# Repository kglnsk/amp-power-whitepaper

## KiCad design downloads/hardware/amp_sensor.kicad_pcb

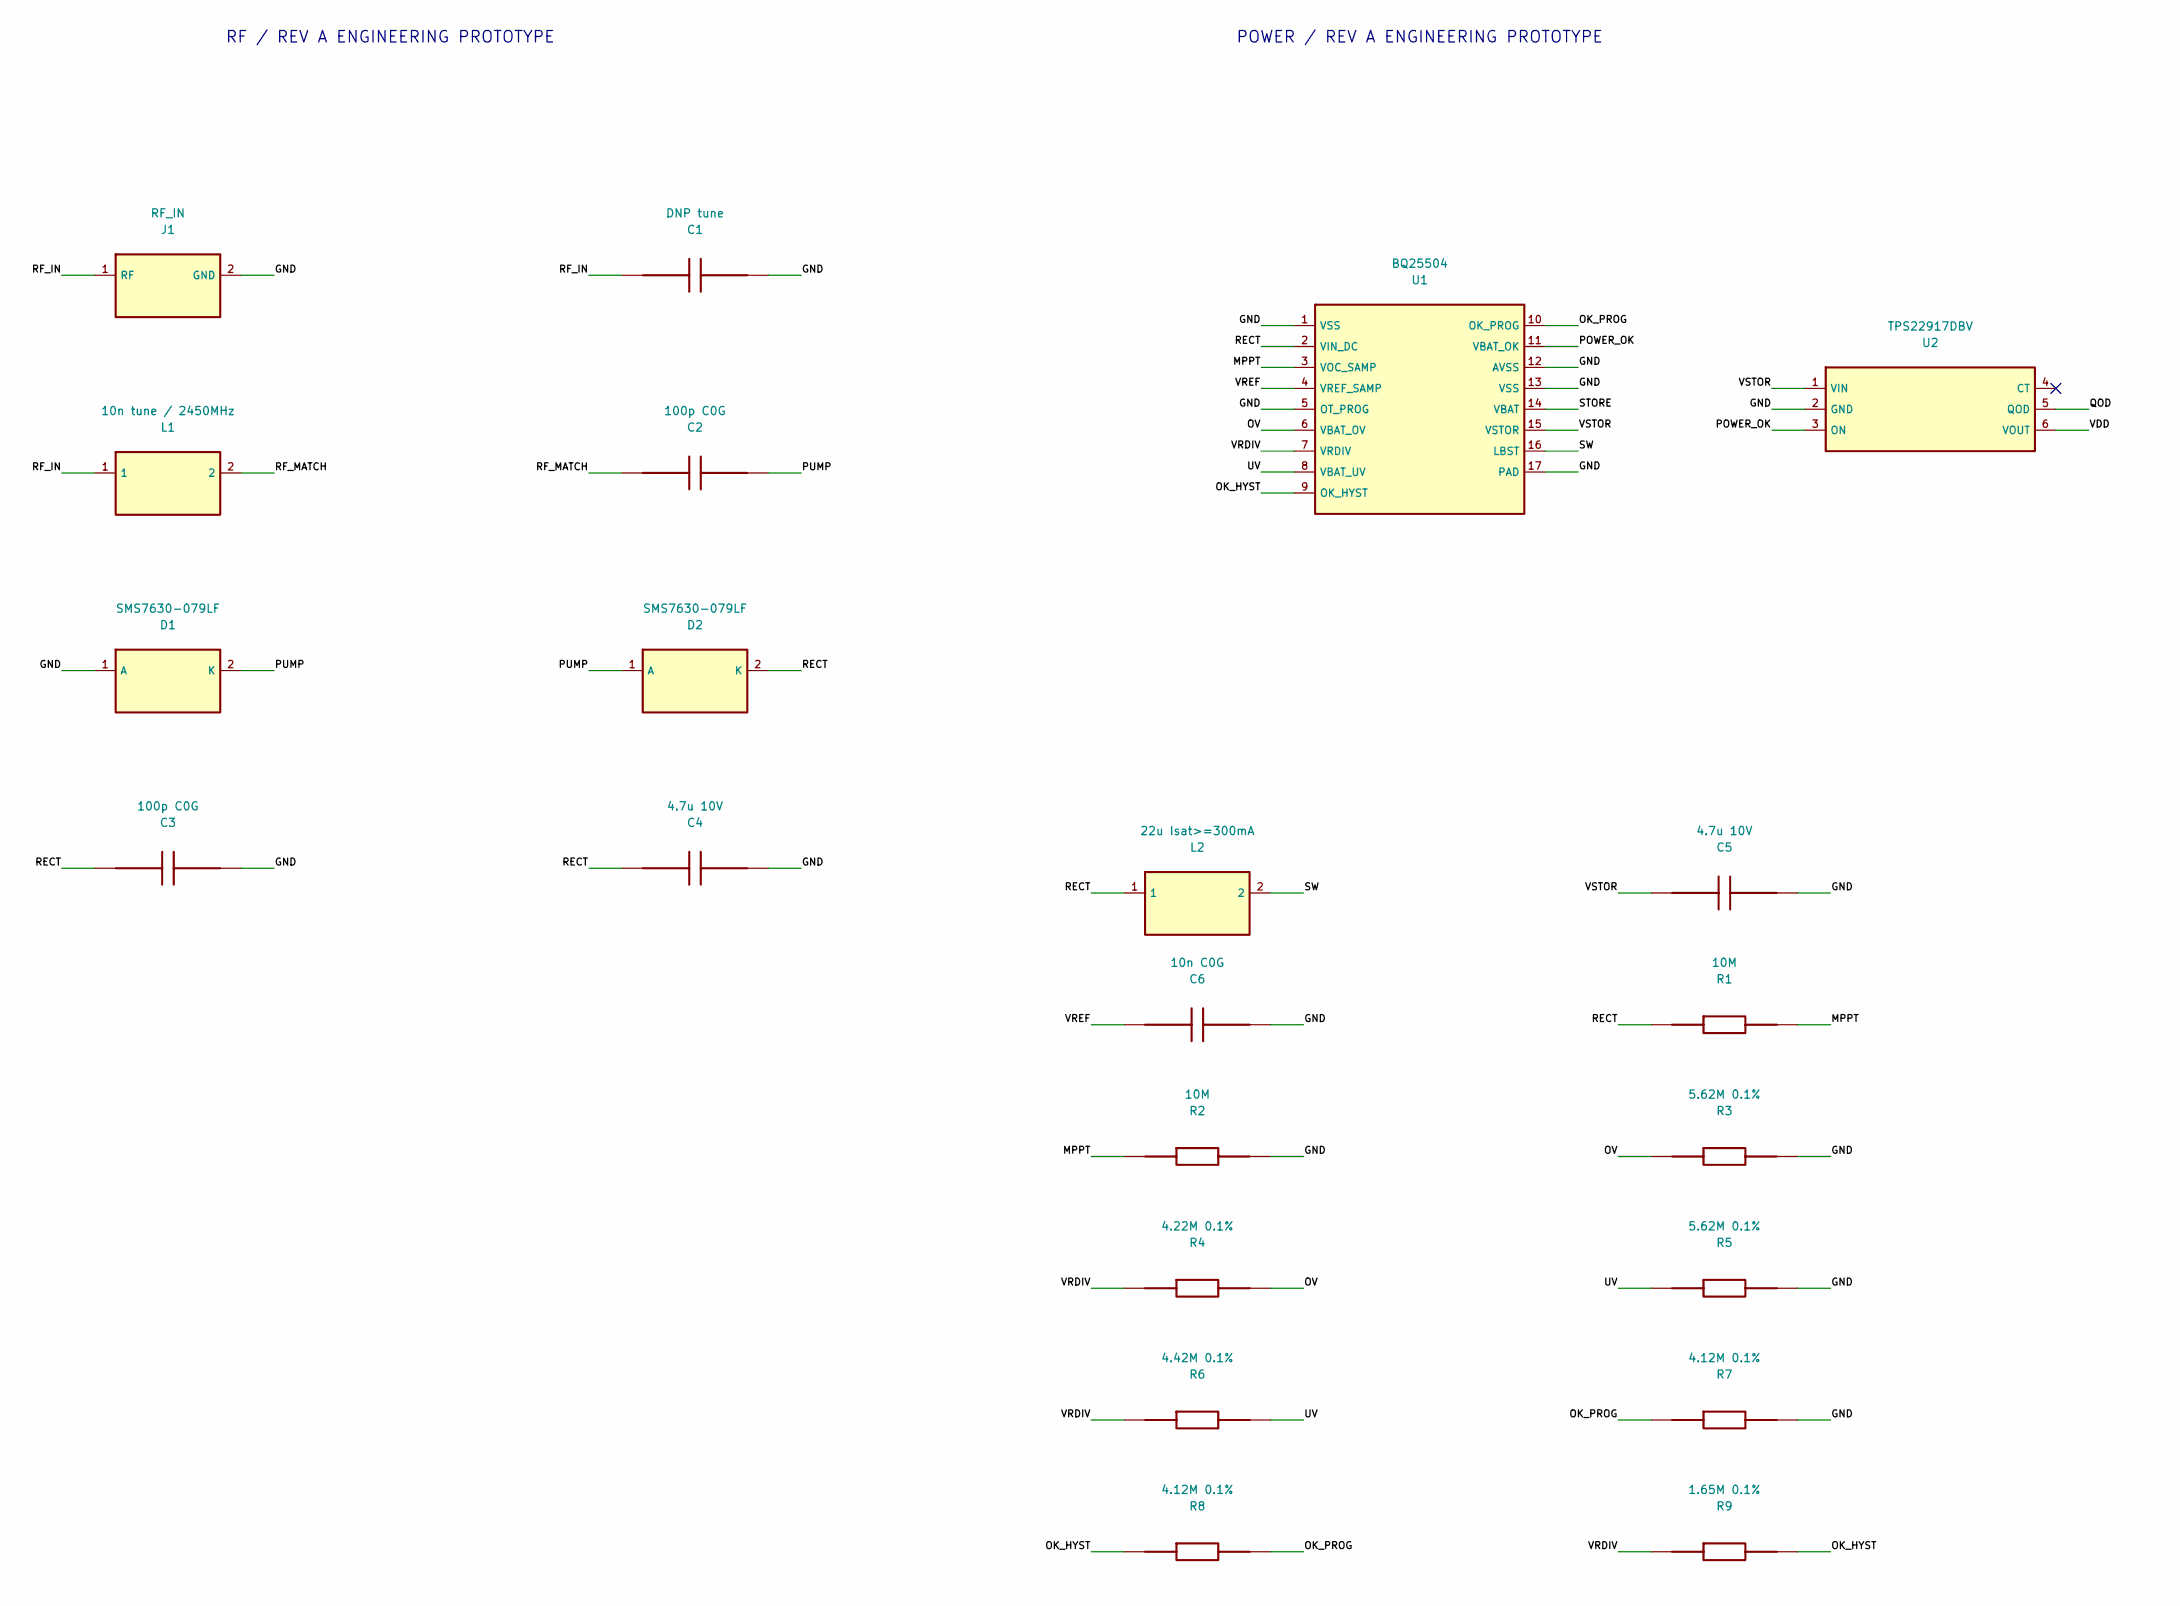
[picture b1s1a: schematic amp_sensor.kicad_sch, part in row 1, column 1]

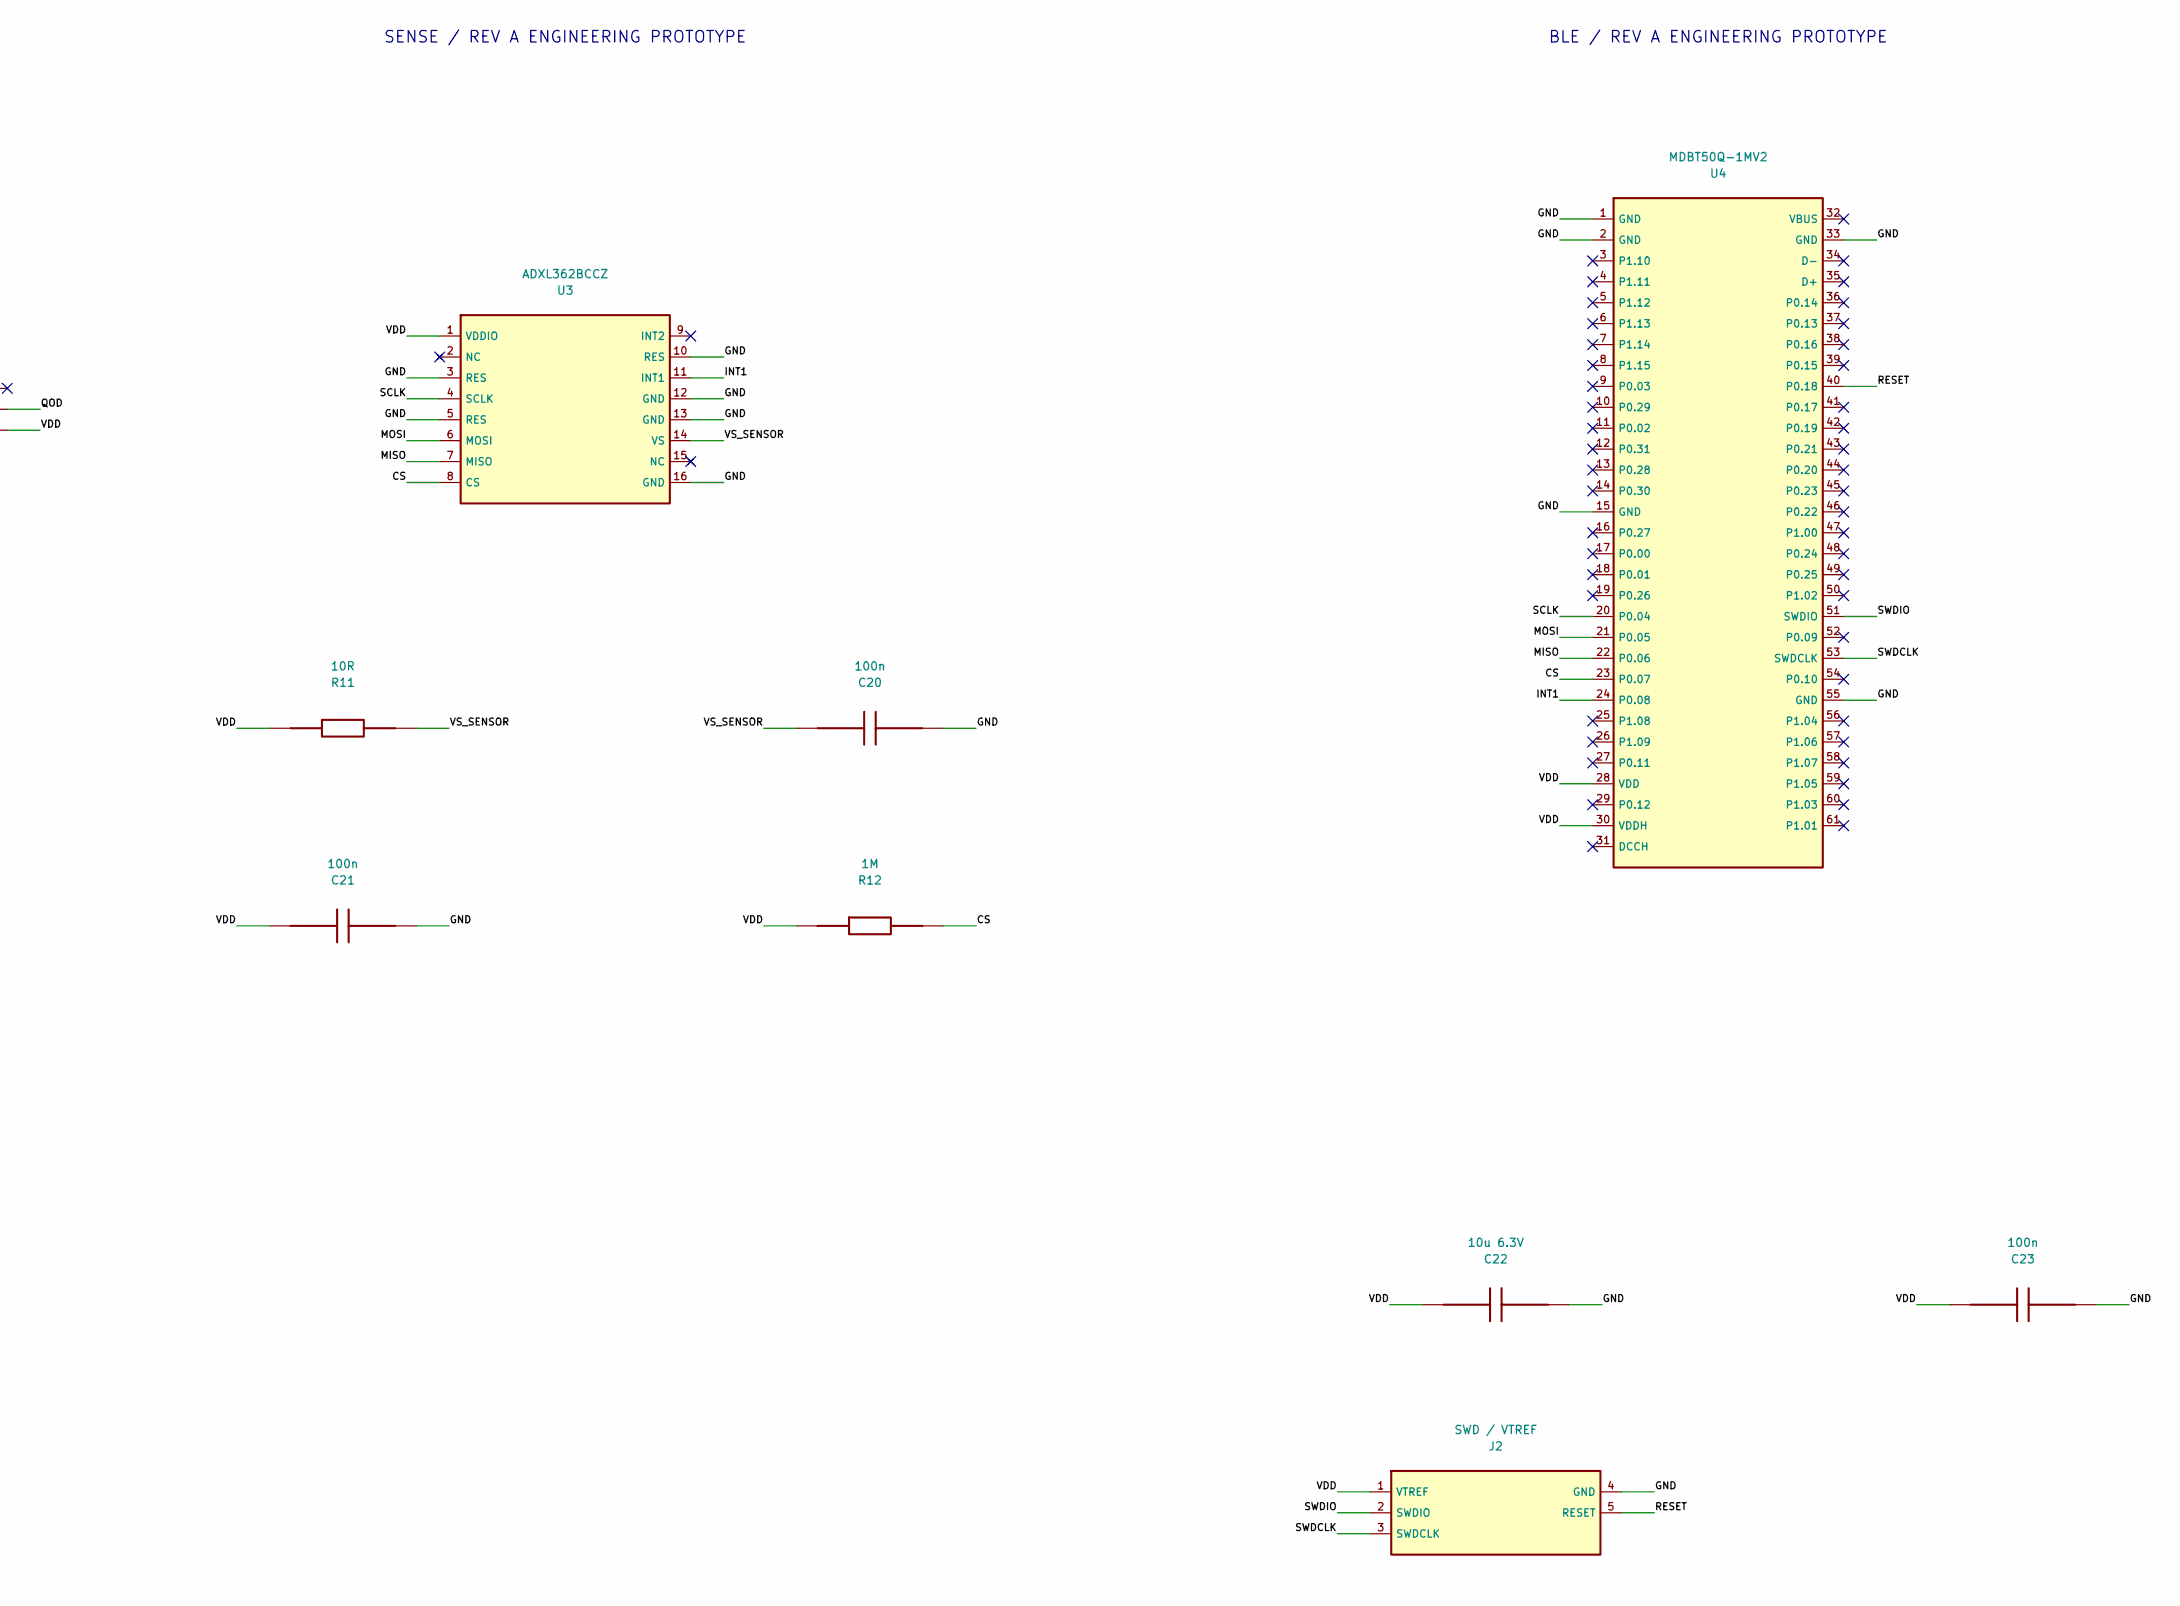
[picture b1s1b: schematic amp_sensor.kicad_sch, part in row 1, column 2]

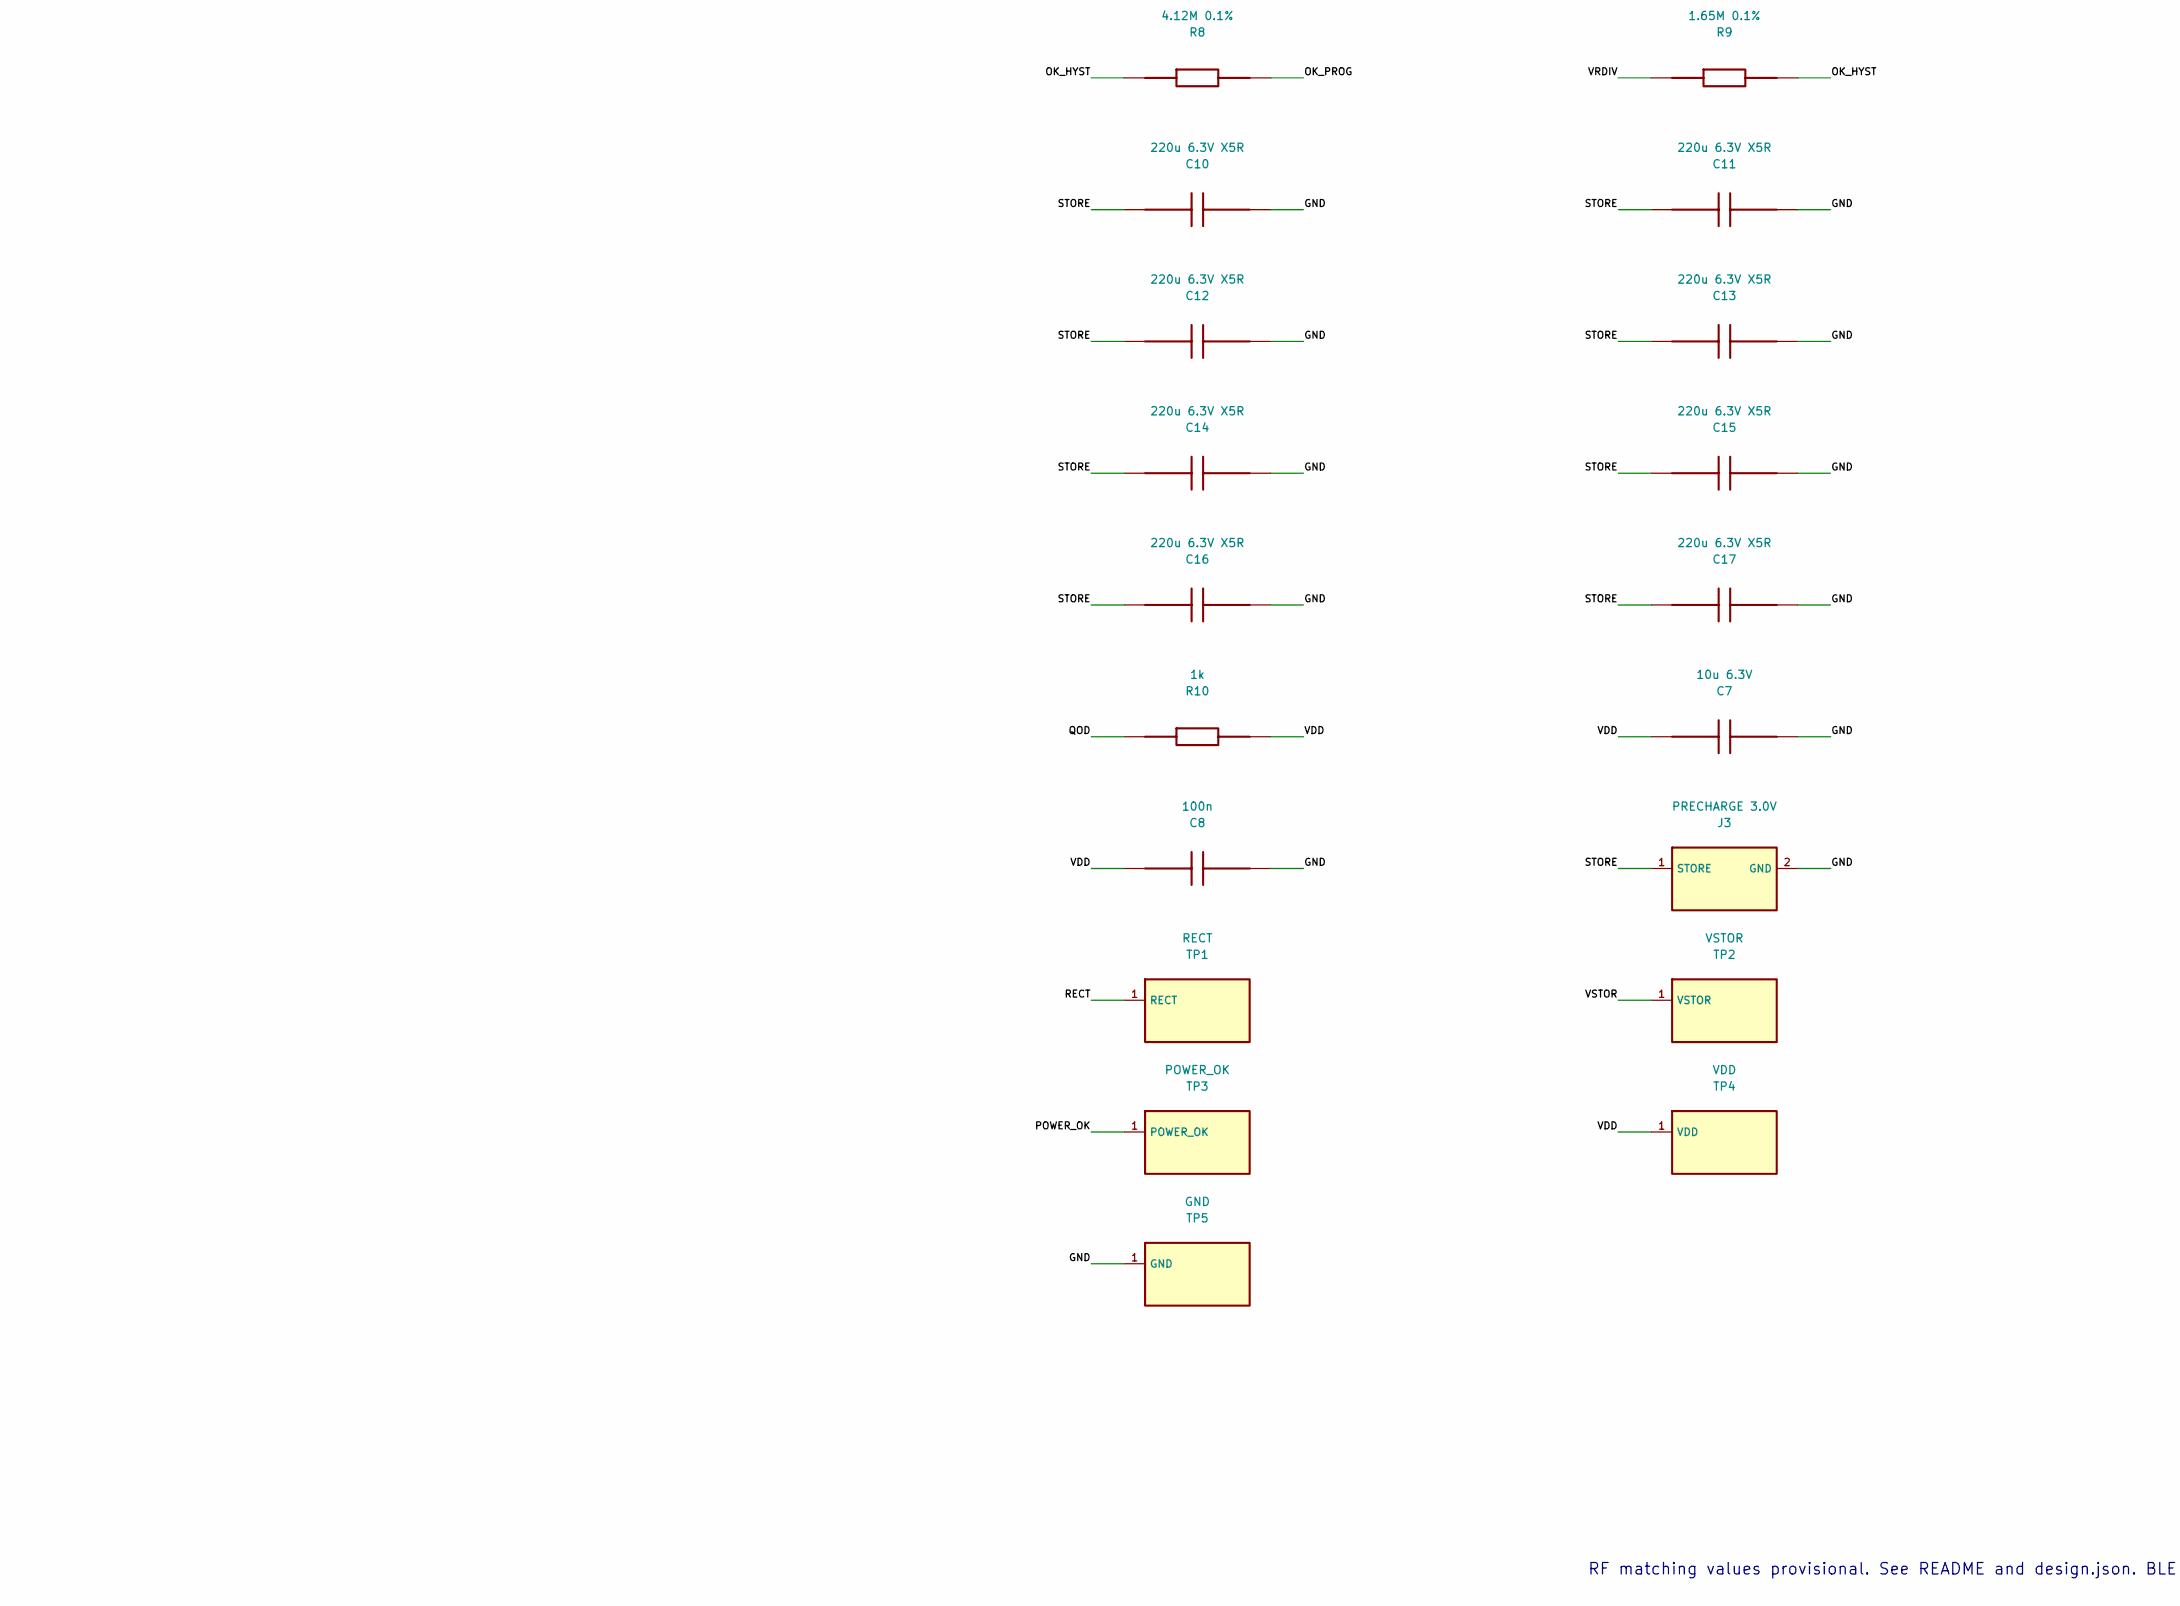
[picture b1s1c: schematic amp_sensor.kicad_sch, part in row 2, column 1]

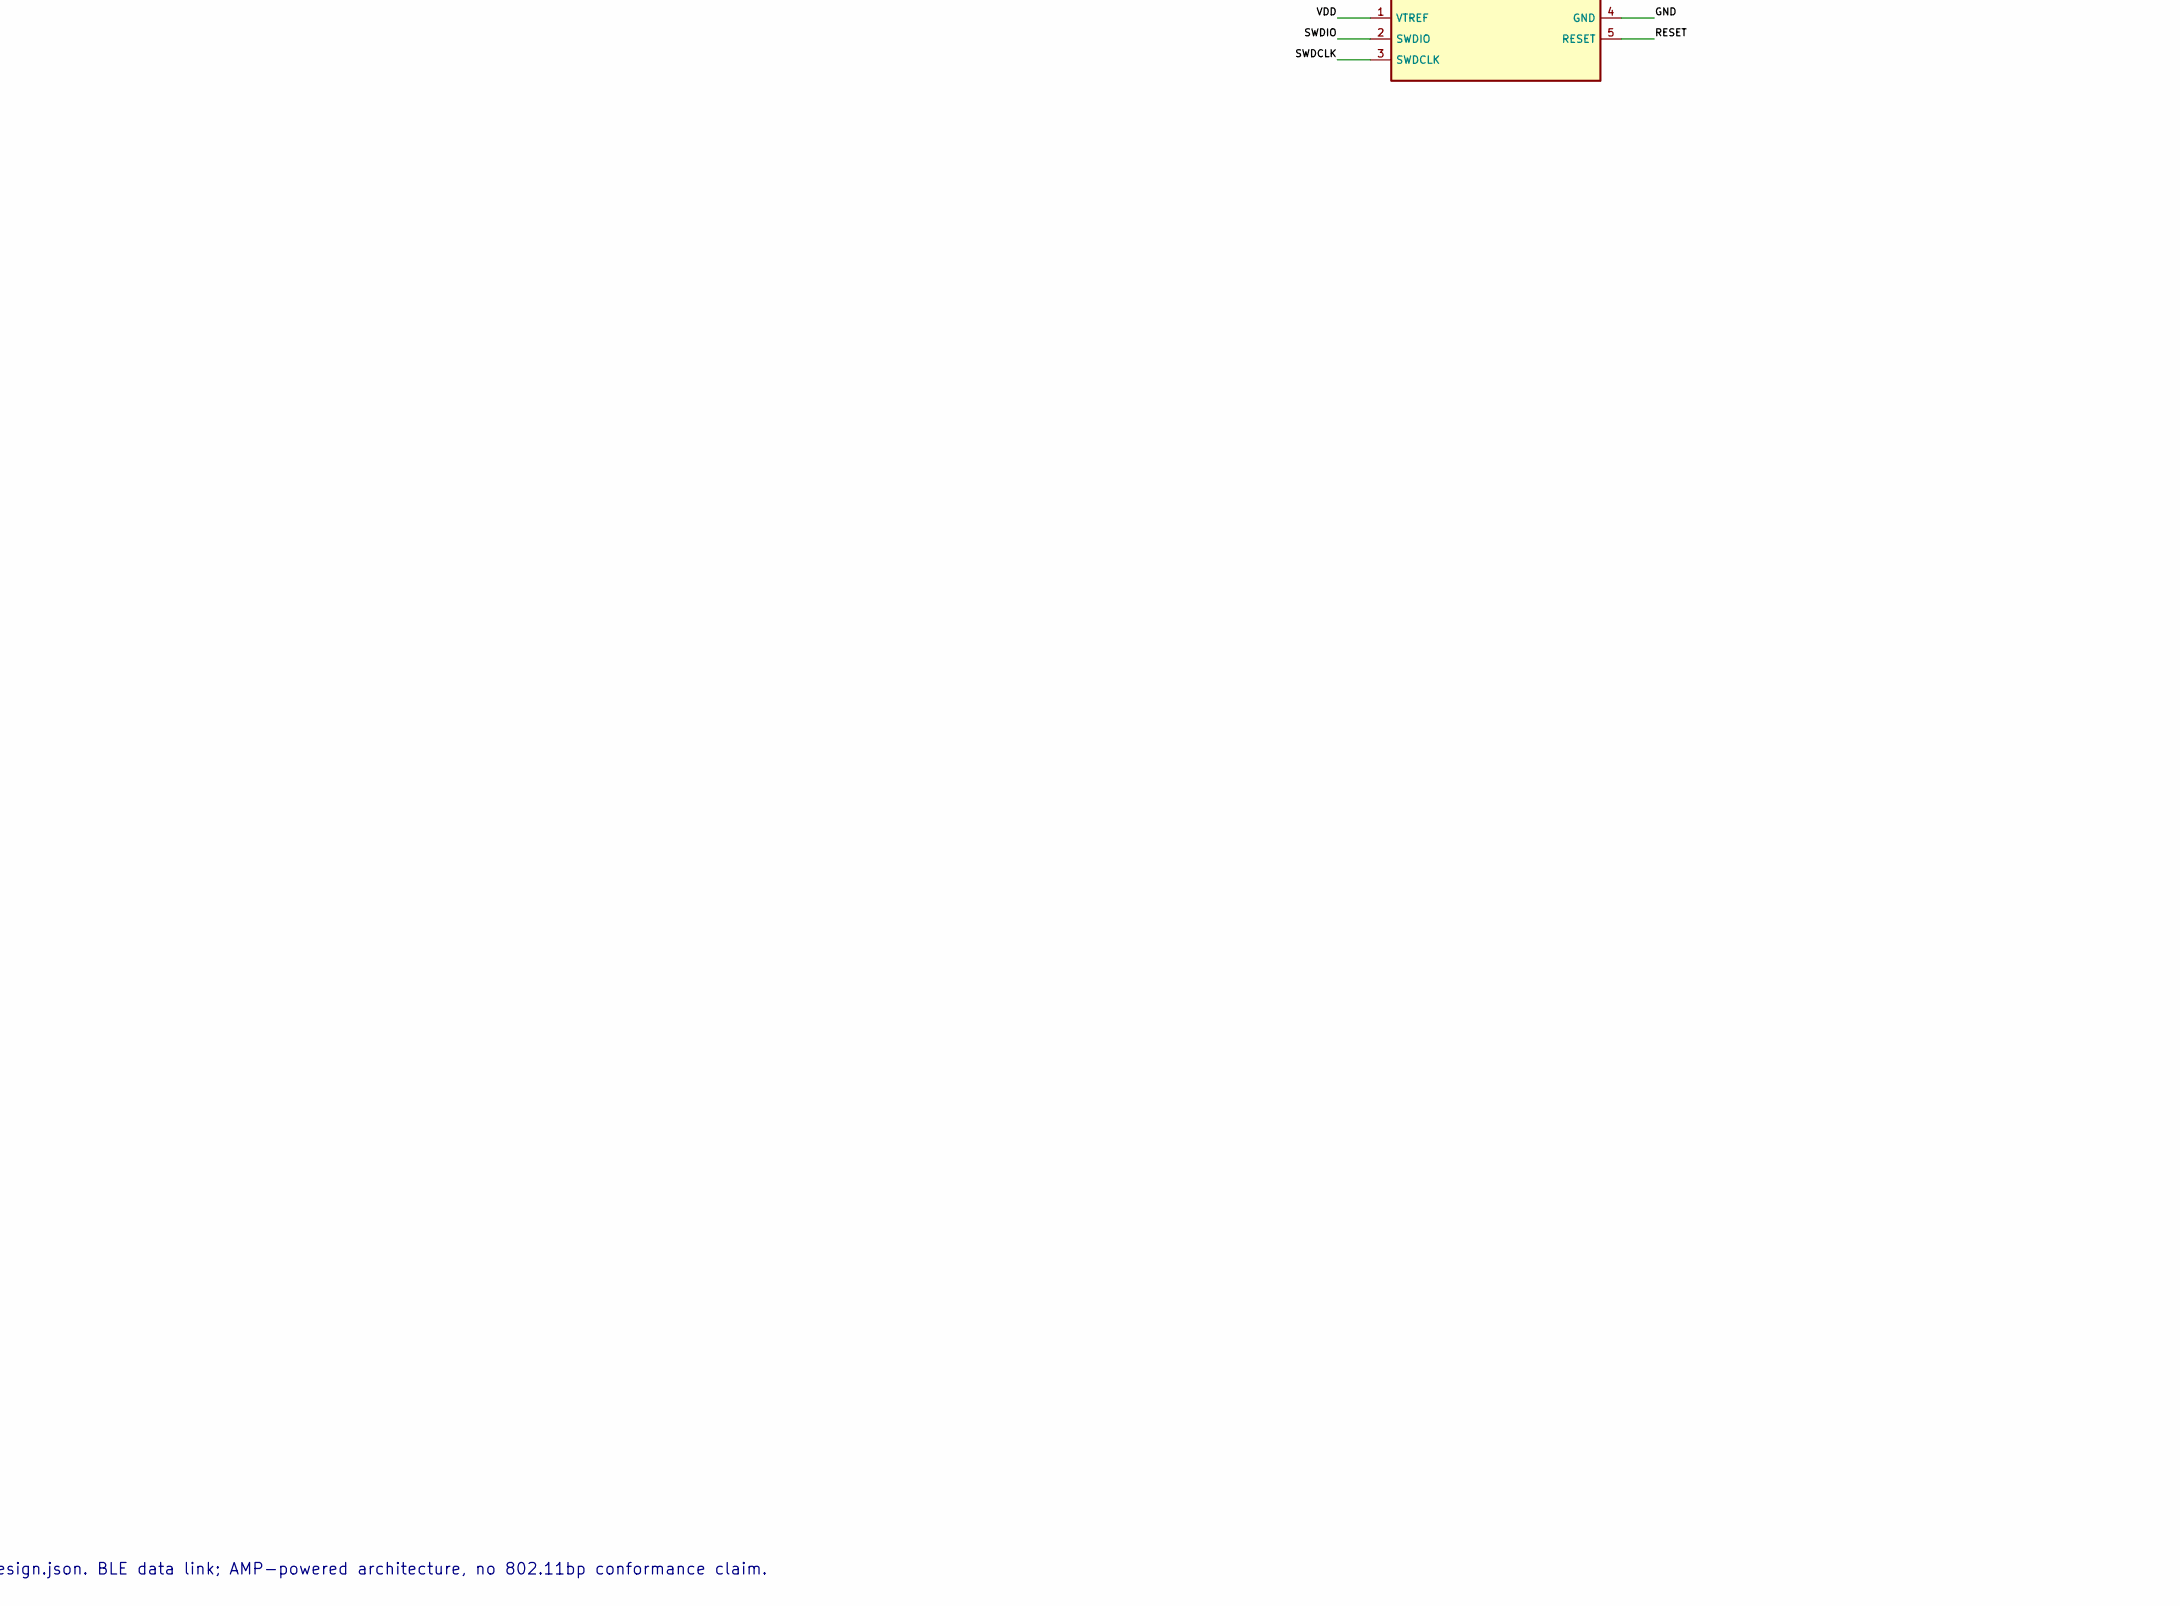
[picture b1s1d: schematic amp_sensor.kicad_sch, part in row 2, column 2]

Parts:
C1: DNP tune; C_0603_1608Metric
C2, C3: 100p C0G; C_0603_1608Metric
C4, C5: 4.7u 10V; C_0603_1608Metric
C6: 10n C0G; C_0603_1608Metric
C7, C22: 10u 6.3V; C_0603_1608Metric
C8, C20, C21, C23: 100n; C_0603_1608Metric
C10, C11, C12, C13, C14, C15, C16, C17: 220u 6.3V X5R; C_1210_3225Metric
D1, D2: SMS7630-079LF; SC79
J1: RF_IN; U.FL_Hirose_U.FL-R-SMT-1_Vertical
J2: SWD / VTREF; PinHeader_1x05_P2.54mm_Vertical
J3: PRECHARGE 3.0V; PinHeader_1x02_P2.54mm_Vertical
L1: 10n tune / 2450MHz; L_0603_1608Metric
L2: 22u Isat>=300mA; L_Taiyo-Yuden_NR-40xx
R1, R2: 10M; R_0603_1608Metric
R3, R5: 5.62M 0.1%; R_0603_1608Metric
R4: 4.22M 0.1%; R_0603_1608Metric
R6: 4.42M 0.1%; R_0603_1608Metric
R7, R8: 4.12M 0.1%; R_0603_1608Metric
R9: 1.65M 0.1%; R_0603_1608Metric
R10: 1k; R_0603_1608Metric
R11: 10R; R_0603_1608Metric
R12: 1M; R_0603_1608Metric
TP1: RECT; TestPoint_Pad_D1.0mm
TP2: VSTOR; TestPoint_Pad_D1.0mm
TP3: POWER_OK; TestPoint_Pad_D1.0mm
TP4: VDD; TestPoint_Pad_D1.0mm
TP5: GND; TestPoint_Pad_D1.0mm
U1: BQ25504; VQFN-16-1EP_3x3mm_P0.5mm_EP1.68x1.68mm
U2: TPS22917DBV; SOT-23-6
U3: ADXL362BCCZ; Analog_LGA-16_3.25x3mm_P0.5mm_LayoutBorder3x5y
U4: MDBT50Q-1MV2; Raytac_MDBT50Q

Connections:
CS: R12.2, U3.8 (CS), U4.23 (P0.07)
GND: C1.2, C3.2, C4.2, C5.2, C6.2, C7.2, C8.2, C10.2, C11.2, C12.2, C13.2, C14.2, C15.2, C16.2, C17.2, C20.2, C21.2, C22.2, C23.2, D1.1 (A), J1.2 (GND), J2.4 (GND), J3.2 (GND), R2.2, R3.2, R5.2, R7.2, TP5.1, U1.1 (VSS), U1.5 (OT_PROG), U1.12 (AVSS), U1.13 (VSS), U1.17 (PAD), U2.2 (GND), U3.3 (RES), U3.5 (RES), U3.10 (RES), U3.12 (GND), U3.13 (GND), U3.16 (GND), U4.1 (GND), U4.2 (GND), U4.15 (GND), U4.33 (GND), U4.55 (GND)
INT1: U3.11 (INT1), U4.24 (P0.08)
MISO: U3.7 (MISO), U4.22 (P0.06)
MOSI: U3.6 (MOSI), U4.21 (P0.05)
MPPT: R1.2, R2.1, U1.3 (VOC_SAMP)
OK_HYST: R8.1, R9.2, U1.9 (OK_HYST)
OK_PROG: R7.1, R8.2, U1.10 (OK_PROG)
OV: R3.1, R4.2, U1.6 (VBAT_OV)
POWER_OK: TP3.1, U1.11 (VBAT_OK), U2.3 (ON)
PUMP: C2.2, D1.2 (K), D2.1 (A)
QOD: R10.1, U2.5 (QOD)
RECT: C3.1, C4.1, D2.2 (K), L2.1, R1.1, TP1.1, U1.2 (VIN_DC)
RESET: J2.5 (RESET), U4.40 (P0.18)
RF_IN: C1.1, J1.1 (RF), L1.1
RF_MATCH: C2.1, L1.2
SCLK: U3.4 (SCLK), U4.20 (P0.04)
STORE: C10.1, C11.1, C12.1, C13.1, C14.1, C15.1, C16.1, C17.1, J3.1 (STORE), U1.14 (VBAT)
SW: L2.2, U1.16 (LBST)
SWDCLK: J2.3 (SWDCLK), U4.53 (SWDCLK)
SWDIO: J2.2 (SWDIO), U4.51 (SWDIO)
UV: R5.1, R6.2, U1.8 (VBAT_UV)
VDD: C7.1, C8.1, C21.1, C22.1, C23.1, J2.1 (VTREF), R10.2, R11.1, R12.1, TP4.1, U2.6 (VOUT), U3.1 (VDDIO), U4.28 (VDD), U4.30 (VDDH)
VRDIV: R4.1, R6.1, R9.1, U1.7 (VRDIV)
VREF: C6.1, U1.4 (VREF_SAMP)
VSTOR: C5.1, TP2.1, U1.15 (VSTOR), U2.1 (VIN)
VS_SENSOR: C20.1, R11.2, U3.14 (VS)

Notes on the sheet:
RF / REV A ENGINEERING PROTOTYPE
POWER / REV A ENGINEERING PROTOTYPE
SENSE / REV A ENGINEERING PROTOTYPE
BLE / REV A ENGINEERING PROTOTYPE
RF matching values provisional. See README and design.json. BLE data link; AMP-powered architecture, no 802.11bp conformance claim.

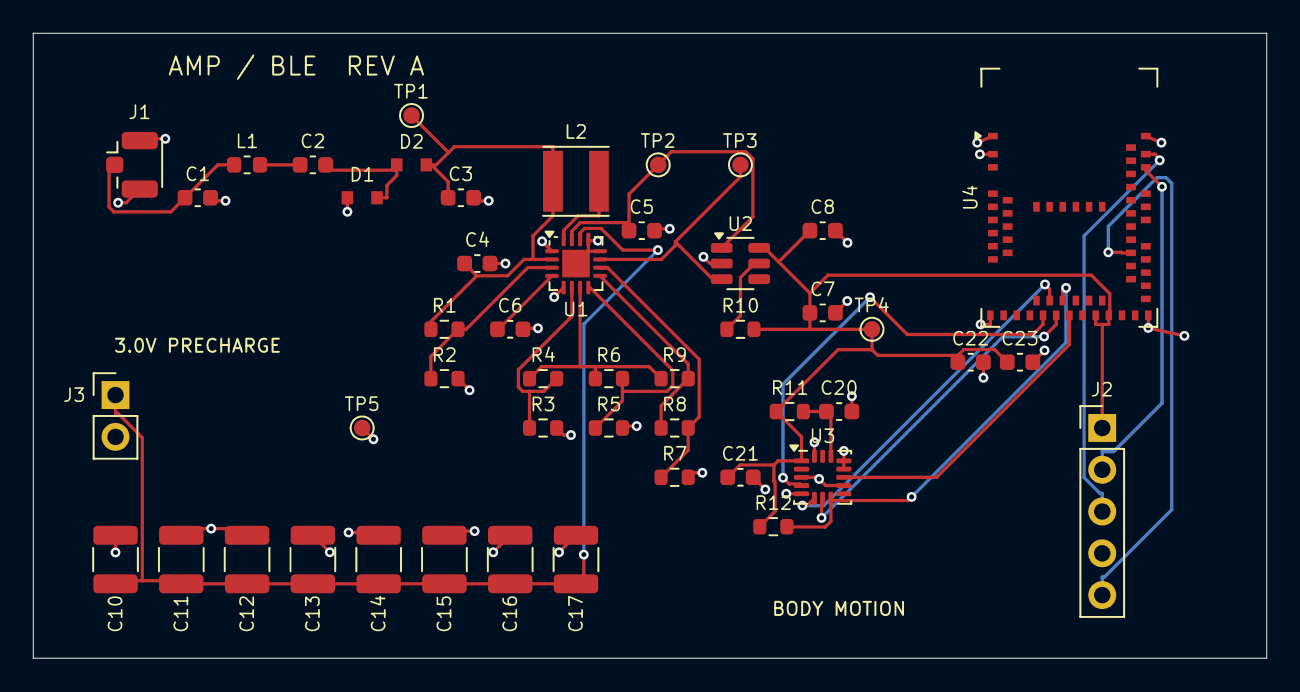
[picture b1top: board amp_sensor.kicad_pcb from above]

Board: 2 copper layers, 75.0 x 38.0 mm, 48 parts (0 on the bottom side), 27 nets.

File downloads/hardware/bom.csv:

Reference,Value / MPN,Footprint,Notes
J1,RF_IN,Connector_Coaxial:U.FL_Hirose_U.FL-R-SMT-1_Vertical,
C1,DNP tune,Capacitor_SMD:C_0603_1608Metric,"Shunt matching; tune with nonlinear load, initially unpopulated"
L1,10n tune / 2450MHz,Inductor_SMD:L_0603_1608Metric,2.45 GHz nominal 10n; 915 MHz variant 68n; tune on assembled PCB
C2,100p C0G,Capacitor_SMD:C_0603_1608Metric,
D1,SMS7630-079LF,AMP:SC79,"SC79; package Ls 0.7 nH; band marks ANODE, not cathode"
D2,SMS7630-079LF,AMP:SC79,
C3,100p C0G,Capacitor_SMD:C_0603_1608Metric,
C4,4.7u 10V,Capacitor_SMD:C_0603_1608Metric,
U1,BQ25504,Package_DFN_QFN:VQFN-16-1EP_3x3mm_P0.5mm_EP1.68x1.68mm,
L2,22u Isat>=300mA,Inductor_SMD:L_Taiyo-Yuden_NR-40xx,
C5,4.7u 10V,Capacitor_SMD:C_0603_1608Metric,
C6,10n C0G,Capacitor_SMD:C_0603_1608Metric,
R1,10M,Resistor_SMD:R_0603_1608Metric,
R2,10M,Resistor_SMD:R_0603_1608Metric,
R3,5.62M 0.1%,Resistor_SMD:R_0603_1608Metric,
R4,4.22M 0.1%,Resistor_SMD:R_0603_1608Metric,
R5,5.62M 0.1%,Resistor_SMD:R_0603_1608Metric,
R6,4.42M 0.1%,Resistor_SMD:R_0603_1608Metric,
R7,4.12M 0.1%,Resistor_SMD:R_0603_1608Metric,
R8,4.12M 0.1%,Resistor_SMD:R_0603_1608Metric,
R9,1.65M 0.1%,Resistor_SMD:R_0603_1608Metric,
C10,220u 6.3V X5R,Capacitor_SMD:C_1210_3225Metric,8 x 220u nominal; design assumes 880u total effective after DC bias; qualify vendor curve
C11,220u 6.3V X5R,Capacitor_SMD:C_1210_3225Metric,8 x 220u nominal; design assumes 880u total effective after DC bias; qualify vendor curve
C12,220u 6.3V X5R,Capacitor_SMD:C_1210_3225Metric,8 x 220u nominal; design assumes 880u total effective after DC bias; qualify vendor curve
C13,220u 6.3V X5R,Capacitor_SMD:C_1210_3225Metric,8 x 220u nominal; design assumes 880u total effective after DC bias; qualify vendor curve
C14,220u 6.3V X5R,Capacitor_SMD:C_1210_3225Metric,8 x 220u nominal; design assumes 880u total effective after DC bias; qualify vendor curve
C15,220u 6.3V X5R,Capacitor_SMD:C_1210_3225Metric,8 x 220u nominal; design assumes 880u total effective after DC bias; qualify vendor curve
C16,220u 6.3V X5R,Capacitor_SMD:C_1210_3225Metric,8 x 220u nominal; design assumes 880u total effective after DC bias; qualify vendor curve
C17,220u 6.3V X5R,Capacitor_SMD:C_1210_3225Metric,8 x 220u nominal; design assumes 880u total effective after DC bias; qualify vendor curve
U2,TPS22917DBV,Package_TO_SOT_SMD:SOT-23-6,
R10,1k,Resistor_SMD:R_0603_1608Metric,Output discharge when off; verify ADXL362 off interval >=200ms and rise-time on oscilloscope
C7,10u 6.3V,Capacitor_SMD:C_0603_1608Metric,
C8,100n,Capacitor_SMD:C_0603_1608Metric,
U3,ADXL362BCCZ,Sensor_Motion:Analog_LGA-16_3.25x3mm_P0.5mm_LayoutBorder3x5y,
R11,10R,Resistor_SMD:R_0603_1608Metric,
C20,100n,Capacitor_SMD:C_0603_1608Metric,
C21,100n,Capacitor_SMD:C_0603_1608Metric,
R12,1M,Resistor_SMD:R_0603_1608Metric,
U4,MDBT50Q-1MV2,RF_Module:Raytac_MDBT50Q,nRF52840; normal-voltage supply VDD=VDDH; DCCH/VBUS/USB NC; internal LFRC initially; module includes RF matching
C22,10u 6.3V,Capacitor_SMD:C_0603_1608Metric,
C23,100n,Capacitor_SMD:C_0603_1608Metric,
J2,SWD / VTREF,Connector_PinHeader_2.54mm:PinHeader_1x05_P2.54mm_Vertical,VTREF is sense only; disconnect debugger for power measurement
J3,PRECHARGE 3.0V,Connector_PinHeader_2.54mm:PinHeader_1x02_P2.54mm_Vertical,Current-limited bench precharge; not USB or 5V
TP1,RECT,TestPoint:TestPoint_Pad_D1.0mm,
TP2,VSTOR,TestPoint:TestPoint_Pad_D1.0mm,
TP3,POWER_OK,TestPoint:TestPoint_Pad_D1.0mm,
TP4,VDD,TestPoint:TestPoint_Pad_D1.0mm,
TP5,GND,TestPoint:TestPoint_Pad_D1.0mm,
